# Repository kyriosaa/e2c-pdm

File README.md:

# E2C-PDM — An edge-to-cloud digital twin for predictive maintenance

Thesis project. A three-tier condition-monitoring system built around a
laboratory motor rig: an ESP32-S3 acquisition front-end, a Raspberry Pi
inference tier, and a cloud tier for the digital twin and long-horizon storage.

**Status: data acquisition validated, healthy baseline recorded, no fault data
yet.** The offline feature pipeline runs end to end. Model training is blocked on
seeded-fault data — see
[docs/notes/collection_protocol.md](docs/notes/collection_protocol.md).

---

## Architecture

```
   MOTOR RIG                 EDGE TIER 1            EDGE TIER 2        CLOUD
   ---------                 -----------            -----------        -----
  RS-445PA DC motor
  + BTS7960 driver
        |
  IIS3DWB   26.7 kHz x3 ---+
  INMP441   16 kHz mono ---+--> ESP32-S3 ----USB CDC----> Raspberry Pi ---> InfluxDB
  MLX90614  1 Hz -------- +    (FreeRTOS,   ~200 KB/s    (features,        + digital
                               2 cores,                   inference,         twin
                               raw counts)                cascade gate)
                                    |
                            thermal interlock
                            70 C latched kill
```

Design principle: computation is pushed to the cheapest place. The MCU ships raw
sensor counts and does no unit conversion or feature extraction, which keeps it a
deterministic acquisition front-end and keeps the acquisition path identical
between dataset collection and deployment.

The ESP32→Pi link is infrastructure and is **excluded** from the bandwidth-savings
claim; that claim applies to the Pi→cloud tier only.

## Repository layout

```
edge/
  esp32/firmware/mdc/                  acquisition + safety firmware
  esp32/tools/                         data_catcher.py (host logger), notifier, start_handler
  hardware/edge_asset_monitor_2L/      2-layer PCB, lab-etched (KiCad)
  hardware/edge_asset_monitor_4L/      4-layer PCB + gerbers (KiCad)
  hardware/espressif-kicad-addon/      VENDORED third-party library, see its README
  rpi/                                 Pi-tier scaffolding (early)
cloud/                                 cloud-tier scaffolding (early)
ml/                                    offline pipeline -- see ml/README.md
  studies/                             one-off analyses (audio filtering, integrity)
  notebooks/                           exploratory notebooks
data/                                  UNTRACKED. raw/ interim/ processed/
docs/
  notes/                               decisions + rationale + the quirk
                                       register. READ THIS FIRST.
  figures/                             tracked thesis figures (pipeline/ is generated)
  datasheets/ certifications/          RS-445PA, IIS3DWB, STEVAL-MKI208V1K,
                                       ISO 13732-1, ...
  schematics/ images/                  rev1.0 and rev2.0
references.md                          reference paper bank
```

`data/` is gitignored; sessions are ~4.5 GB each. `docs/notes/` is gitignored
too, so **the design notes linked below are local-only and will not be present
in a clone.** `docs/figures/pipeline/` is gitignored as the pipeline regenerates
it; the rest of `docs/` is tracked.

## Getting oriented

Start with [docs/notes/](docs/notes/):

| Note | What it settles |
|---|---|
| [quirk_register.md](docs/notes/quirk_register.md) | **Read before quoting any number.** The real dataset inventory, known defects, and the measured sensor calibration. |
| [collection_protocol.md](docs/notes/collection_protocol.md) | **How to collect data from here on.** The confound trap, the fault set, the integrity gate. |
| [operating_profile_rationale.md](docs/notes/operating_profile_rationale.md) | Why the rig needs no "real" use case, and what it does need. |
| [motor_signature.md](docs/notes/motor_signature.md) | Measured spectrum, measured sample rates, rig validation against physics. |
| [thermal_channel_confound.md](docs/notes/thermal_channel_confound.md) | Why absolute temperature is unusable and the thermal channel is currently flat. |
| [acoustic_noise_filtering.md](docs/notes/acoustic_noise_filtering.md) | Why spectral subtraction, and why not a notch or high-pass. |
| [overnight_acquisition_rig.md](docs/notes/overnight_acquisition_rig.md) | Acquisition architecture, integrity layers, safety layers, defence Q&A. |
| [thermal_interlock_70c.md](docs/notes/thermal_interlock_70c.md) | Why 70 °C, from ISO 13732-1. |

## Reproducing a recording session

Requires the physical rig. Read
[overnight_acquisition_rig.md](docs/notes/overnight_acquisition_rig.md) §3
before running unattended.

1. Flash `edge/esp32/firmware/mdc/` to the ESP32-S3.
   **Never flash with the 24 V rail energised.** Power sequence: USB first, 24 V
   last; de-energise 24 V first.
2. Set the run parameters and provenance fields at the top of
   `edge/esp32/tools/data_catcher.py` — `SESSION_LABEL`, `RUN_SECONDS`,
   `MOTOR_VOLTAGE_V`, `MECHANICAL_LOAD`, `FAULT_CONDITION`, `ROOM_CONDITION`.
   `ACCEL_FS_G` must match the firmware.
3. `python edge/esp32/tools/data_catcher.py`
   The motor arms after `ARM_DELAY_S` (60 s); that head of the recording is the
   motor-off room-noise reference. No logger means no motor — the firmware
   requires an explicit host arm.
4. Output lands in `data/raw/<label>_<timestamp>/`: `vibration.bin`, `audio.wav`,
   `status.csv`, `packet_index.csv`, `session.json`.
5. Gate the session on integrity before trusting it:
   ```
   python -m ml.sessions <session_name>
   python -m ml.studies.integrity_report
   ```
   Acceptance criteria are in
   [collection_protocol.md](docs/notes/collection_protocol.md).

## Running the offline pipeline

From the repository root. See [ml/README.md](ml/README.md) for detail.

```
pip install -r ml/requirements.txt

python -m ml.sessions                 # gap map + measured sample rates (cached)
python -m ml.data_loader              # per-session sanity check
python -m ml.features                 # gap-aware Welch PSD windows
python -m ml.studies.integrity_report # dataset integrity table

# leave-one-session-out, training pool held to one operating point so the 15 V
# session stays unseen for the novelty check
python -m ml.train_autoencoder --split session \
    --sessions healthy24V_motor_baseline_20260718_001741 \
               healthy24V_motor_baseline_20260719_010905 \
    --holdout  healthy24V_motor_baseline_20260719_010905
python -m ml.evaluate --novelty healthy15V_motor_baseline_20260716_002156
python -m ml.quantize                 # TFLite dynamic + int8
```

Feature extraction needs only numpy + scipy. **Training needs TensorFlow, which
has no Python 3.14 wheels** — use a separate 3.12 environment for the last three
steps; cached features are reusable across both. See ml/README.md.

## Secrets

Copy `.env.example` to `.env` and fill it in. `.env` is gitignored and is the only
place credentials belong.

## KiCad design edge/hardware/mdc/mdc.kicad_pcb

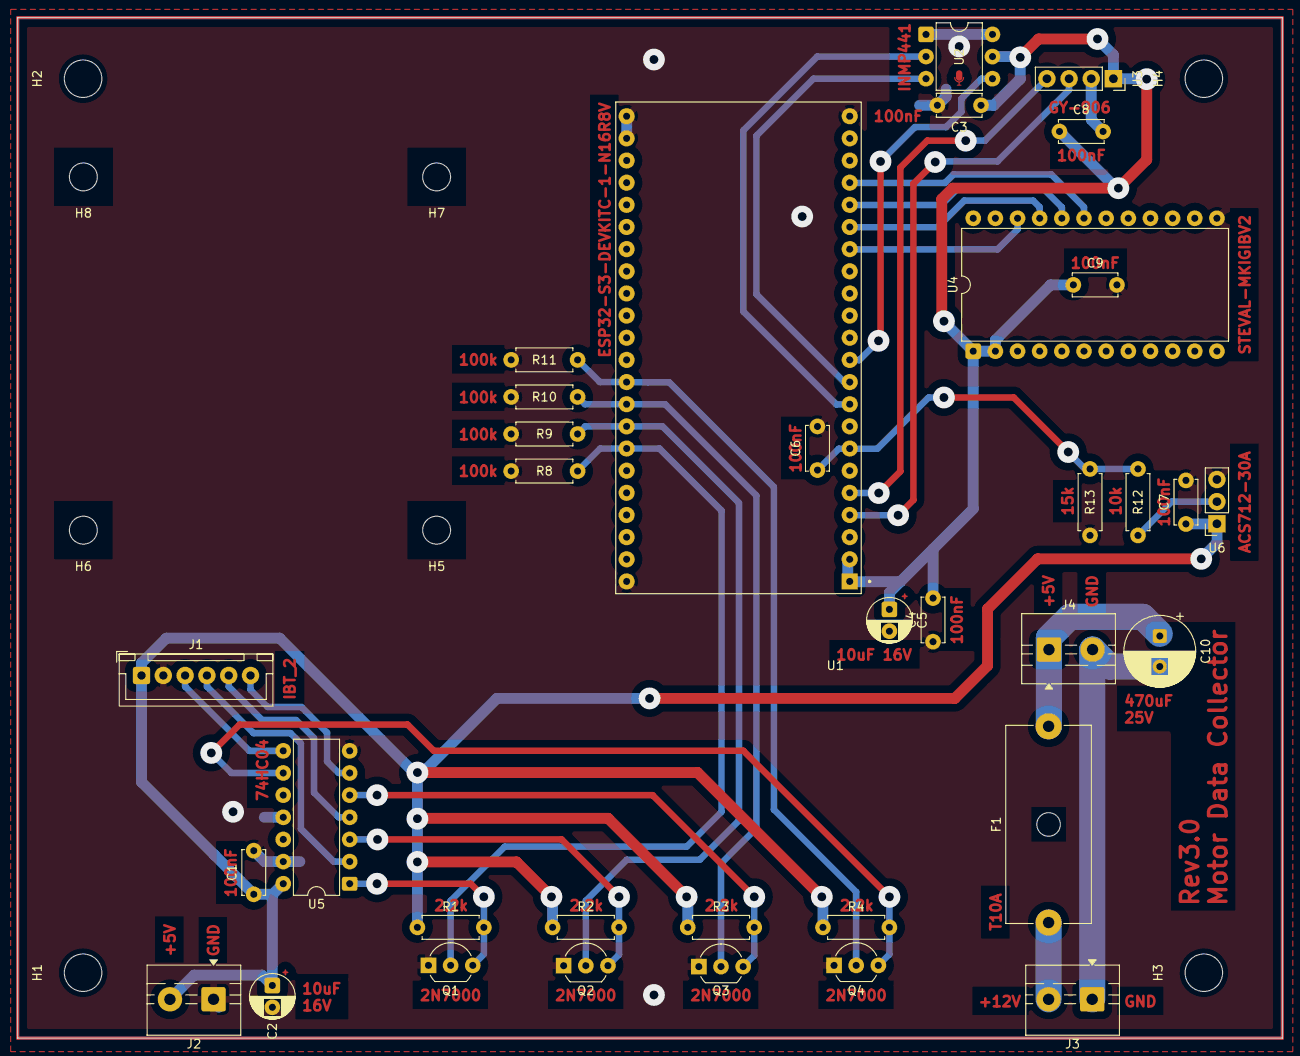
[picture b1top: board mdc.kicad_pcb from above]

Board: 2 copper layers, 145.0 x 117.0 mm, 43 parts (0 on the bottom side), 29 nets.

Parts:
C1, C3, C4, C6, C7, C8, C9: 100nF; C_Disc_D5.0mm_W2.5mm_P5.00mm
C2, C5: 10uF 16V; CP_Radial_D5.0mm_P2.50mm
C10: 470uF 25V; CP_Radial_D8.0mm_P3.50mm
F1: T10A; Fuseholder_Cylinder-5x20mm_Schurter_0031_8201_Horizontal_Op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
H1, H2, H3, H4: MountingHole; MountingHole_4.3mm_M4
H5, H6, H7, H8: MountingHole; MountingHole_3.2mm_M3
J1: Conn_01x06; JST_XH_B6B-XH-A_1x06_P2.50mm_Vertical
J2, J3, J4: Conn_01x02; TerminalBlock_MaiXu_MX126-5.0-02P_1x02_P5.00mm
Q1, Q2, Q3, Q4: 2N7000; TO-92_Inline_Wide
R1, R2, R3, R4: 2.2k; R_Axial_DIN0207_L6.3mm_D2.5mm_P7.62mm_Horizontal
R8, R9, R10, R11: 100k; R_Axial_DIN0207_L6.3mm_D2.5mm_P7.62mm_Horizontal
R12: 10k; R_Axial_DIN0207_L6.3mm_D2.5mm_P7.62mm_Horizontal
R13: 15k; R_Axial_DIN0207_L6.3mm_D2.5mm_P7.62mm_Horizontal
U1: ESP32-S3-DEVKITC-1-N16R8V; XCVR_ESP32-S3-DEVKITC-1-N16R8V
U2: INMP441; DIP-6_W7.62mm
U3: GY-906; PinSocket_1x04_P2.54mm_Vertical
U4: STEVAL-MKIGIBV2; DIP-24_W15.24mm
U5: 74HC04; DIP-14_W7.62mm
U6: ACS712-30A; PinSocket_1x03_P2.54mm_Vertical

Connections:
+3V3: C3.1, C4.2, C5.1, C8.1, C9.1, U1.J1_1 (3V3), U1.J1_2 (3V3), U2.5 (VDD), U3.1 (VIN), U4.1 (VDD), U4.2 (VDDIO)
+5V: C1.1, C2.1, C7.1, J1.1, J2.2, R1.1, R2.1, R3.1, R4.1, U5.14 (VCC), U6.1 (VCC)
+12V: F1.1, J3.2
+12V_FUSED: C10.1, F1.2, J4.1
GND: C1.2, C2.2, C3.2, C4.1, C5.2, C6.2, C7.2, C8.2, C9.2, J1.2, J2.1, Q1.1 (S), Q2.1 (S), Q3.1 (S), Q4.1 (S), R8.2, R9.2, R10.2, R11.2, R13.2, U1.J1_22 (GND), U1.J3_1 (GND), U1.J3_21 (GND), U1.J3_22 (GND), U2.1 (L/R), U2.6 (GND), U3.2 (GND), U4.13 (GND), U5.7 (GND), U5.11, U5.13, U6.3 (GND)
GPIO38: Q4.2 (G), R11.1, U1.J3_10 (GPIO38)
GPIO39: Q3.2 (G), R10.1, U1.J3_9 (MTCK/GPIO39)
GPIO40: Q2.2 (G), R9.1, U1.J3_8 (MTDO/GPIO40)
GPIO41: Q1.2 (G), R8.1, U1.J3_7 (MTDI/GPIO41)
I2C_SCL: U1.J1_4 (GPIO4), U3.3 (SCL)
I2C_SDA: U1.J1_5 (GPIO5), U3.4 (SDA)
I2S_SCK: U1.J1_10 (GPIO17), U2.3 (SCK)
I2S_SD: U1.J1_11 (GPIO18), U2.4 (SD)
I2S_WS: U1.J1_9 (GPIO16), U2.2 (WS)
ISENSE: C6.1, R12.2, R13.1, U1.J1_7 (GPIO7)
LPWM: J1.5, U5.4
LPWM_IN: Q2.3 (D), R2.2, U5.3
L_EN: J1.3, U5.8
L_EN_IN: Q4.3 (D), R4.2, U5.9
MOTOR_GND: C10.2, J3.1, J4.2
unnamed: R12.1, U6.2 (OUT)
RPWM: J1.4, U5.2
RPWM_IN: Q1.3 (D), R1.2, U5.1
R_EN: J1.6, U5.6
R_EN_IN: Q3.3 (D), R3.2, U5.5
SPI_CS: U1.J1_19 (GPIO13), U4.19 (CS)
SPI_SCL: U1.J1_18 (GPIO12), U4.20 (SCL)
SPI_SDA: U1.J1_17 (GPIO11), U4.21 (SDA)
SPI_SDO: U1.J1_16 (GPIO10), U4.22 (SDO-SAO)

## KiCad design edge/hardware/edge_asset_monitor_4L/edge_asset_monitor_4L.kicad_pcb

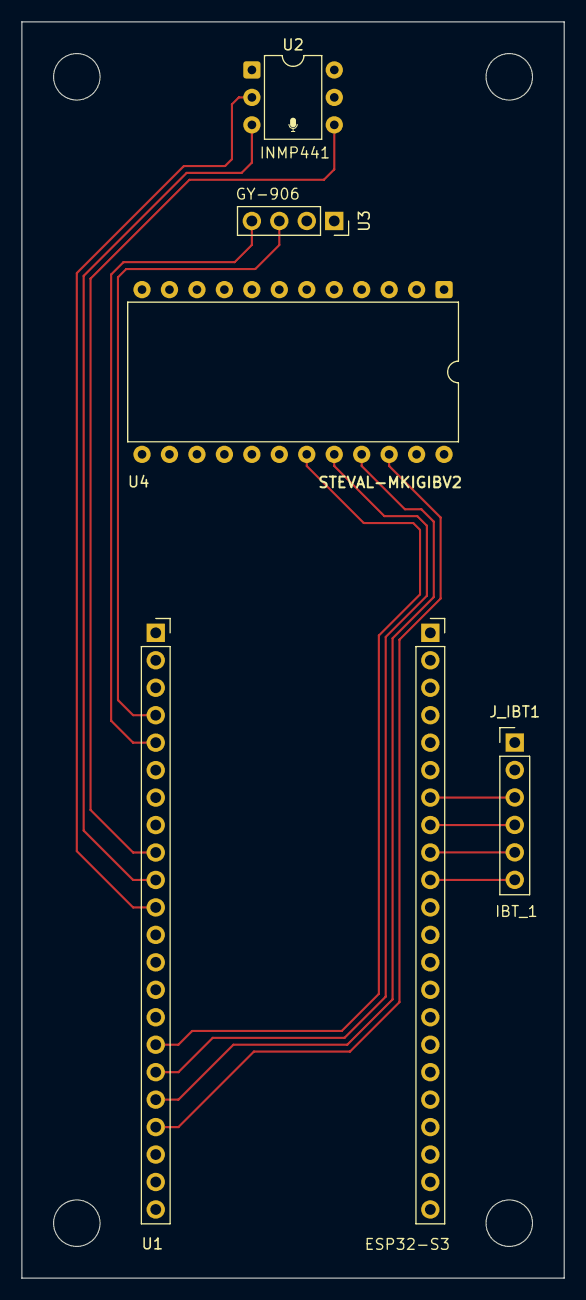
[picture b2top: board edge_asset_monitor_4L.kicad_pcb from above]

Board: 4 copper layers, 50.2 x 116.2 mm, 9 parts (0 on the bottom side), 15 nets.

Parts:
H1, H2, H3, H4: MountingHole; MountingHole_4.3mm_M4
J_IBT1: Conn_01x06_Pin; PinHeader_1x06_P2.54mm_Vertical
U1: ESP32-S3-DEVKITC-1-N16R8V; PinSocket_1x22_P2.54mm_Vertical
U2: DIP-6_W7.62mm
U3: PinSocket_1x04_P2.54mm_Vertical
U4: DIP-24_W15.24mm

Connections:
+3V3: J_IBT1.1, U1.J1_1 (3V3), U1.J1_2 (3V3), U2.5 (VDD), U3.1 (VIN), U4.1 (VDD), U4.2 (VDDIO)
GND: J_IBT1.2, U1.J1_22 (GND), U1.J3_1 (GND), U1.J3_21 (GND), U1.J3_22 (GND), U2.1 (L/R), U2.6 (GND), U3.2 (GND), U4.13 (GND)
unnamed: J_IBT1.3, U1.J3_7 (MTDI/GPIO41)
unnamed: J_IBT1.4, U1.J3_8 (MTDO/GPIO40)
unnamed: J_IBT1.5, U1.J3_9 (MTCK/GPIO39)
unnamed: J_IBT1.6, U1.J3_10 (GPIO38)
unnamed: U1.J1_4 (GPIO4), U3.3 (SCL)
unnamed: U1.J1_5 (GPIO5), U3.4 (SDA)
unnamed: U1.J1_16 (GPIO10), U4.19 (CS)
unnamed: U1.J1_17 (GPIO11), U4.20 (SCL)
unnamed: U1.J1_18 (GPIO12), U4.21 (SDA)
unnamed: U1.J1_19 (GPIO13), U4.22 (SDO-SAO)
unnamed: U1.J1_9 (GPIO16), U2.4 (SD)
unnamed: U1.J1_10 (GPIO17), U2.3 (SCK)
unnamed: U1.J1_11 (GPIO18), U2.2 (WS)

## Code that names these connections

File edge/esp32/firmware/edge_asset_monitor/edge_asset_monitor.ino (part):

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#define IIS3DWB_SDO 10  // MISO

// INMP441 - acoustic (I2S)
#define I2S_SD      18
#define I2S_SCK     17
#define I2S_WS      16
#define I2S_PORT    I2S_NUM_0

// IBT_2 - motor driver
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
